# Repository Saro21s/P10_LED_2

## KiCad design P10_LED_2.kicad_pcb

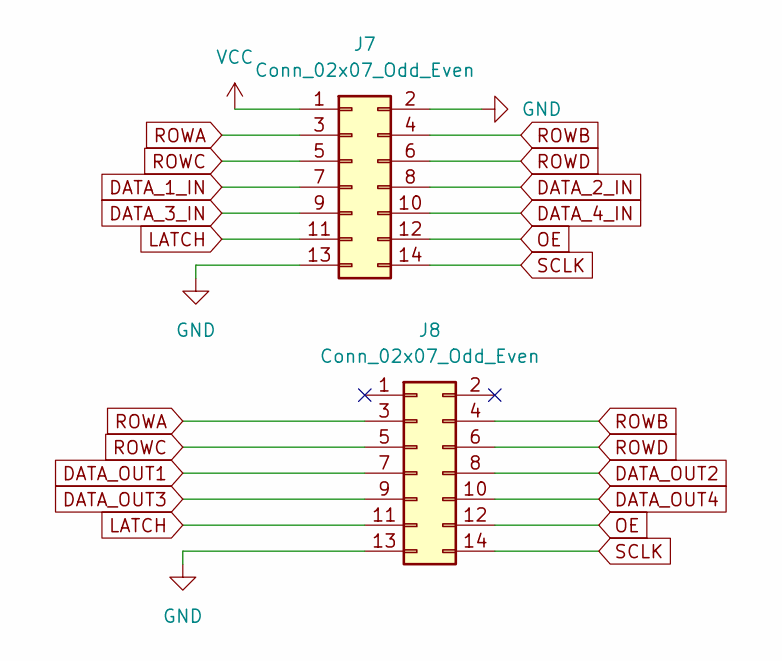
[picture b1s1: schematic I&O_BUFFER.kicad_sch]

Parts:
J7, J8: Conn_02x07_Odd_Even; PinHeader_2x07_P2.00mm_Vertical

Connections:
DATA_1_IN: J7.7; also elsewhere on the board
DATA_2_IN: J7.8; also elsewhere on the board
DATA_3_IN: J7.9; also elsewhere on the board
DATA_4_IN: J7.10; also elsewhere on the board
DATA_OUT1: J8.7; also elsewhere on the board
DATA_OUT2: J8.8; also elsewhere on the board
DATA_OUT3: J8.9; also elsewhere on the board
DATA_OUT4: J8.10; also elsewhere on the board
GND: J7.2, J7.13, J8.13; also elsewhere on the board
LATCH: J7.11, J8.11; also elsewhere on the board
OE: J7.12, J8.12; also elsewhere on the board
ROWA: J7.3, J8.3; also elsewhere on the board
ROWB: J7.4, J8.4; also elsewhere on the board
ROWC: J7.5, J8.5; also elsewhere on the board
ROWD: J7.6, J8.6; also elsewhere on the board
SCLK: J7.14, J8.14; also elsewhere on the board
VCC: J7.1; also elsewhere on the board

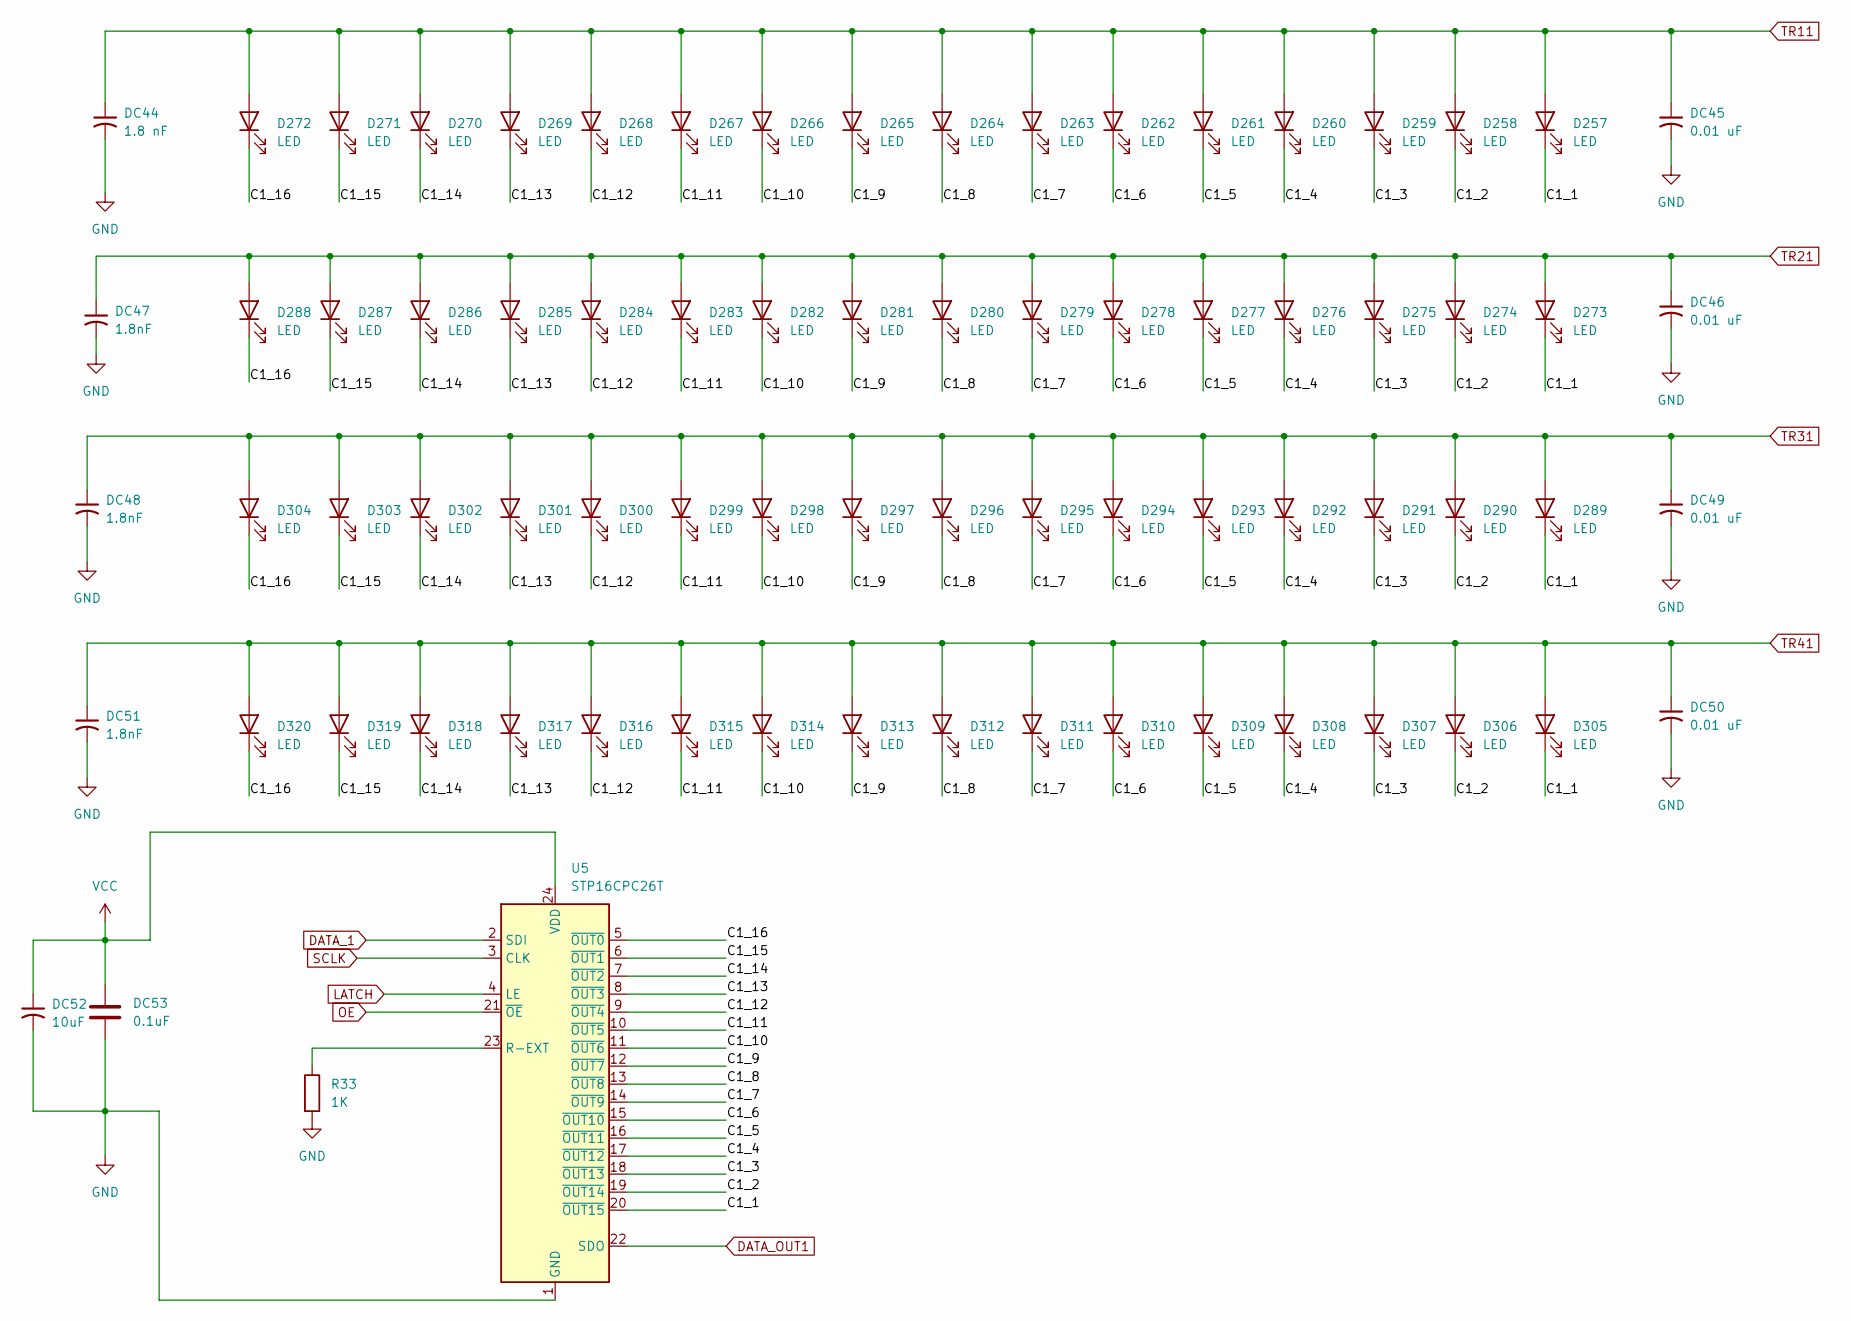
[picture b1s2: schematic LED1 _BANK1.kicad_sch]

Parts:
D257, D258, D259, D260, D261, D262, D263, D264, D265, D266, D267, D268, D269, D270, D271, D272, D273, D274, D275, D276, D277, D278, D279, D280, D281, D282, D283, D284, D285, D286, D287, D288, D289, D290, D291, D292, D293, D294, D295, D296, D297, D298, D299, D300, D301, D302, D303, D304, D305, D306, D307, D308, D309, D310, D311, D312, D313, D314, D315, D316, D317, D318, D319, D320: LED; LED_0805_2012Metric
DC44: 1.8 nF; C_0805_2012Metric
DC45, DC46, DC49, DC50: 0.01 uF; C_0805_2012Metric
DC47, DC48, DC51: 1.8nF; C_0805_2012Metric
DC52: 10uF; C_0805_2012Metric
DC53: 0.1uF; C_0805_2012Metric
R33: 1K; R_0805_2012Metric
U5: STP16CPC26T; TSSOP-24_4.4x7.8mm_P0.65mm

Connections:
/LED1 _BANK1/C1_1: D257.1 (K), D273.1 (K), D289.1 (K), D305.1 (K), U5.20 (~OUT15)
/LED1 _BANK1/C1_2: D258.1 (K), D274.1 (K), D290.1 (K), D306.1 (K), U5.19 (~OUT14)
/LED1 _BANK1/C1_3: D259.1 (K), D275.1 (K), D291.1 (K), D307.1 (K), U5.18 (~OUT13)
/LED1 _BANK1/C1_4: D260.1 (K), D276.1 (K), D292.1 (K), D308.1 (K), U5.17 (~OUT12)
/LED1 _BANK1/C1_5: D261.1 (K), D277.1 (K), D293.1 (K), D309.1 (K), U5.16 (~OUT11)
/LED1 _BANK1/C1_6: D262.1 (K), D278.1 (K), D294.1 (K), D310.1 (K), U5.15 (~OUT10)
/LED1 _BANK1/C1_7: D263.1 (K), D279.1 (K), D295.1 (K), D311.1 (K), U5.14 (~OUT9)
/LED1 _BANK1/C1_8: D264.1 (K), D280.1 (K), D296.1 (K), D312.1 (K), U5.13 (~OUT8)
/LED1 _BANK1/C1_9: D265.1 (K), D281.1 (K), D297.1 (K), D313.1 (K), U5.12 (~OUT7)
/LED1 _BANK1/C1_10: D266.1 (K), D282.1 (K), D298.1 (K), D314.1 (K), U5.11 (~OUT6)
/LED1 _BANK1/C1_11: D267.1 (K), D283.1 (K), D299.1 (K), D315.1 (K), U5.10 (~OUT5)
/LED1 _BANK1/C1_12: D268.1 (K), D284.1 (K), D300.1 (K), D316.1 (K), U5.9 (~OUT4)
/LED1 _BANK1/C1_13: D269.1 (K), D285.1 (K), D301.1 (K), D317.1 (K), U5.8 (~OUT3)
/LED1 _BANK1/C1_14: D270.1 (K), D286.1 (K), D302.1 (K), D318.1 (K), U5.7 (~OUT2)
/LED1 _BANK1/C1_15: D271.1 (K), D287.1 (K), D303.1 (K), D319.1 (K), U5.6 (~OUT1)
/LED1 _BANK1/C1_16: D272.1 (K), D288.1 (K), D304.1 (K), D320.1 (K), U5.5 (~OUT0)
DATA_1: U5.2 (SDI); also elsewhere on the board
DATA_OUT1: U5.22 (SDO); also elsewhere on the board
GND: DC44.2, DC45.2, DC46.2, DC47.2, DC48.2, DC49.2, DC50.2, DC51.2, DC52.2, DC53.2, R33.2, U5.1 (GND); also elsewhere on the board
LATCH: U5.4 (LE); also elsewhere on the board
unnamed: R33.1, U5.23 (R-EXT)
OE: U5.21 (~OE); also elsewhere on the board
SCLK: U5.3 (CLK); also elsewhere on the board
TR11: D257.2 (A), D258.2 (A), D259.2 (A), D260.2 (A), D261.2 (A), D262.2 (A), D263.2 (A), D264.2 (A), D265.2 (A), D266.2 (A), D267.2 (A), D268.2 (A), D269.2 (A), D270.2 (A), D271.2 (A), D272.2 (A), DC44.1, DC45.1; also elsewhere on the board
TR21: D273.2 (A), D274.2 (A), D275.2 (A), D276.2 (A), D277.2 (A), D278.2 (A), D279.2 (A), D280.2 (A), D281.2 (A), D282.2 (A), D283.2 (A), D284.2 (A), D285.2 (A), D286.2 (A), D287.2 (A), D288.2 (A), DC46.1, DC47.1; also elsewhere on the board
TR31: D289.2 (A), D290.2 (A), D291.2 (A), D292.2 (A), D293.2 (A), D294.2 (A), D295.2 (A), D296.2 (A), D297.2 (A), D298.2 (A), D299.2 (A), D300.2 (A), D301.2 (A), D302.2 (A), D303.2 (A), D304.2 (A), DC48.1, DC49.1; also elsewhere on the board
TR41: D305.2 (A), D306.2 (A), D307.2 (A), D308.2 (A), D309.2 (A), D310.2 (A), D311.2 (A), D312.2 (A), D313.2 (A), D314.2 (A), D315.2 (A), D316.2 (A), D317.2 (A), D318.2 (A), D319.2 (A), D320.2 (A), DC50.1, DC51.1; also elsewhere on the board
VCC: DC52.1, DC53.1, U5.24 (VDD); also elsewhere on the board

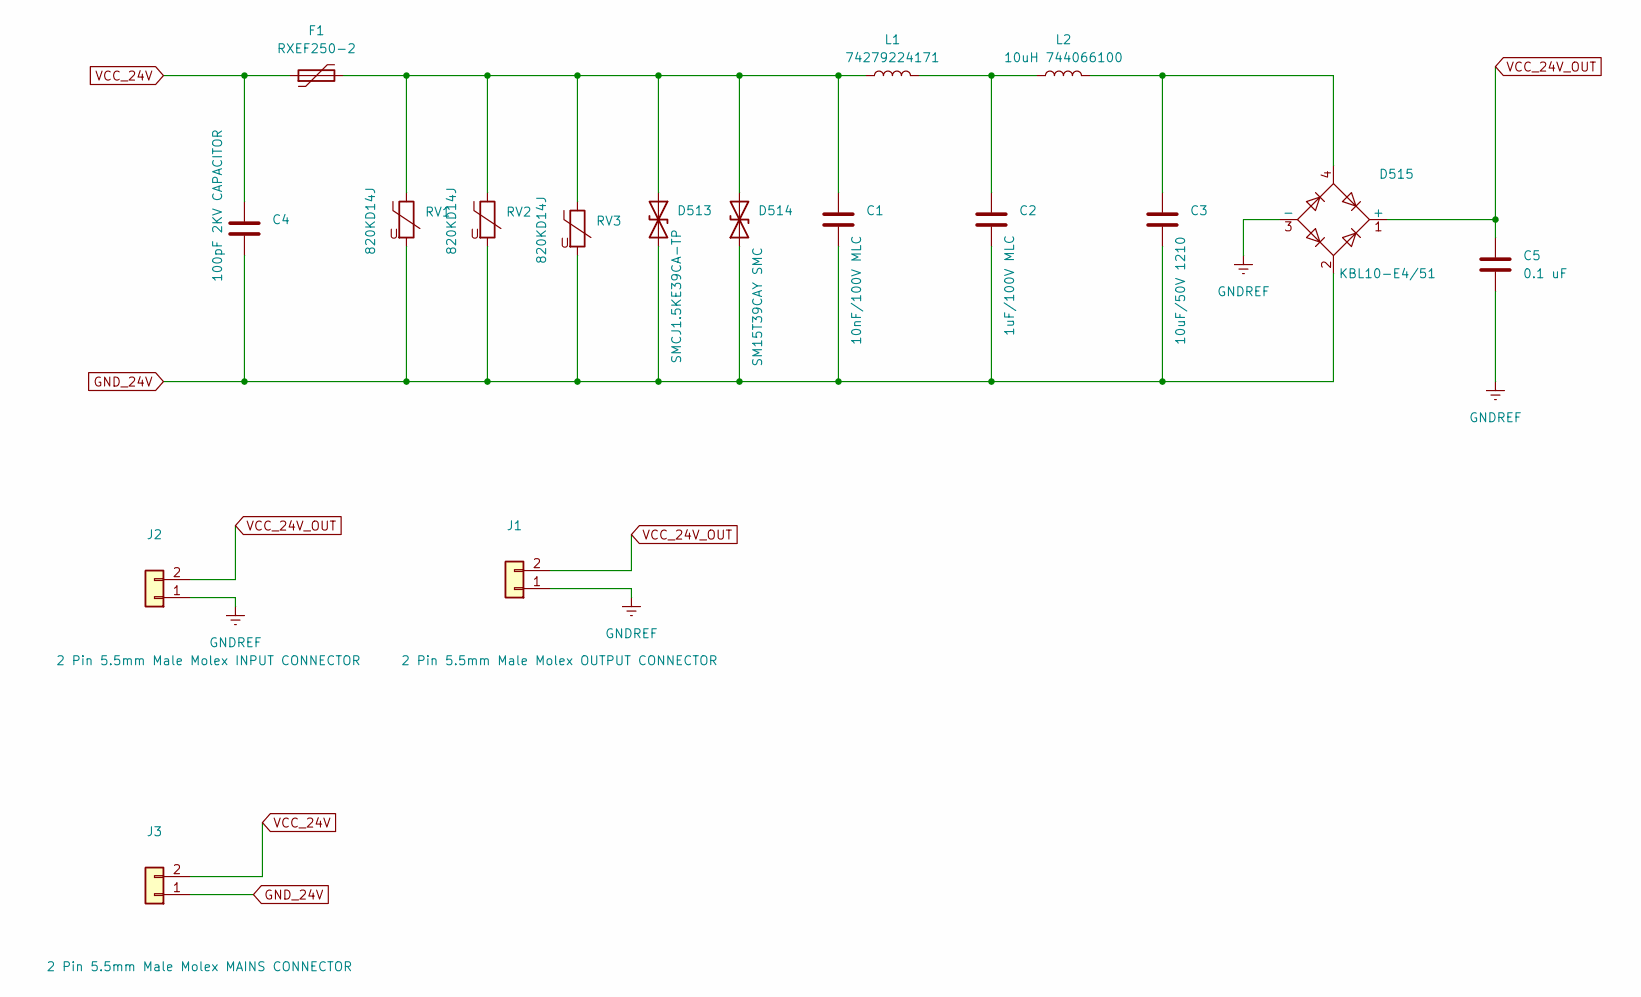
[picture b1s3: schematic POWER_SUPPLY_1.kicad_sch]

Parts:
C1: 10nF/100V MLC; C_1210_3225Metric
C2: 1uF/100V MLC; C_1210_3225Metric
C3: 10uF/50V 1210; C_0805_2012Metric
C4: 100pF 2KV CAPACITOR; C_0805_2012Metric
C5: 0.1 uF; C_1210_3225Metric
D513: SMCJ1.5KE39CA-TP; D_SMC
D514: SM15T39CAY SMC; D_SMC
D515: KBL10-E4/51; Diode_Bridge_Round_D9.8mm
F1: RXEF250-2; Fuse_1812_4532Metric
J1: 2 Pin 5.5mm Male Molex OUTPUT CONNECTOR; Molex_Mini-Fit_Jr_5569-02A1_2x01_P4.20mm_Horizontal
J2: 2 Pin 5.5mm Male Molex INPUT CONNECTOR; Molex_Mini-Fit_Jr_5569-02A1_2x01_P4.20mm_Horizontal
J3: 2 Pin 5.5mm Male Molex MAINS CONNECTOR; Molex_Mini-Fit_Jr_5569-02A1_2x01_P4.20mm_Horizontal
L1: 74279224171; L_1812_4532Metric
L2: 10uH 744066100; L_1812_4532Metric
RV1, RV2, RV3: 820KD14J; RV_Disc_D12mm_W5.8mm_P7.5mm

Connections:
GNDREF: C5.2, D515.3 (-), J1.1, J2.1; also elsewhere on the board
GND_24V: C1.2, C2.2, C3.2, C4.2, D513.2 (A2), D514.1 (A1), D515.2, J3.1, RV1.2, RV2.2, RV3.2
unnamed: C2.1, L1.2, L2.1
unnamed: C3.1, D515.4, L2.2
unnamed: C1.1, D513.1 (A1), D514.2 (A2), F1.2, L1.1, RV1.1, RV2.1, RV3.1
VCC_24V: C4.1, F1.1, J3.2
VCC_24V_OUT: C5.1, D515.1 (+), J1.2, J2.2; also elsewhere on the board

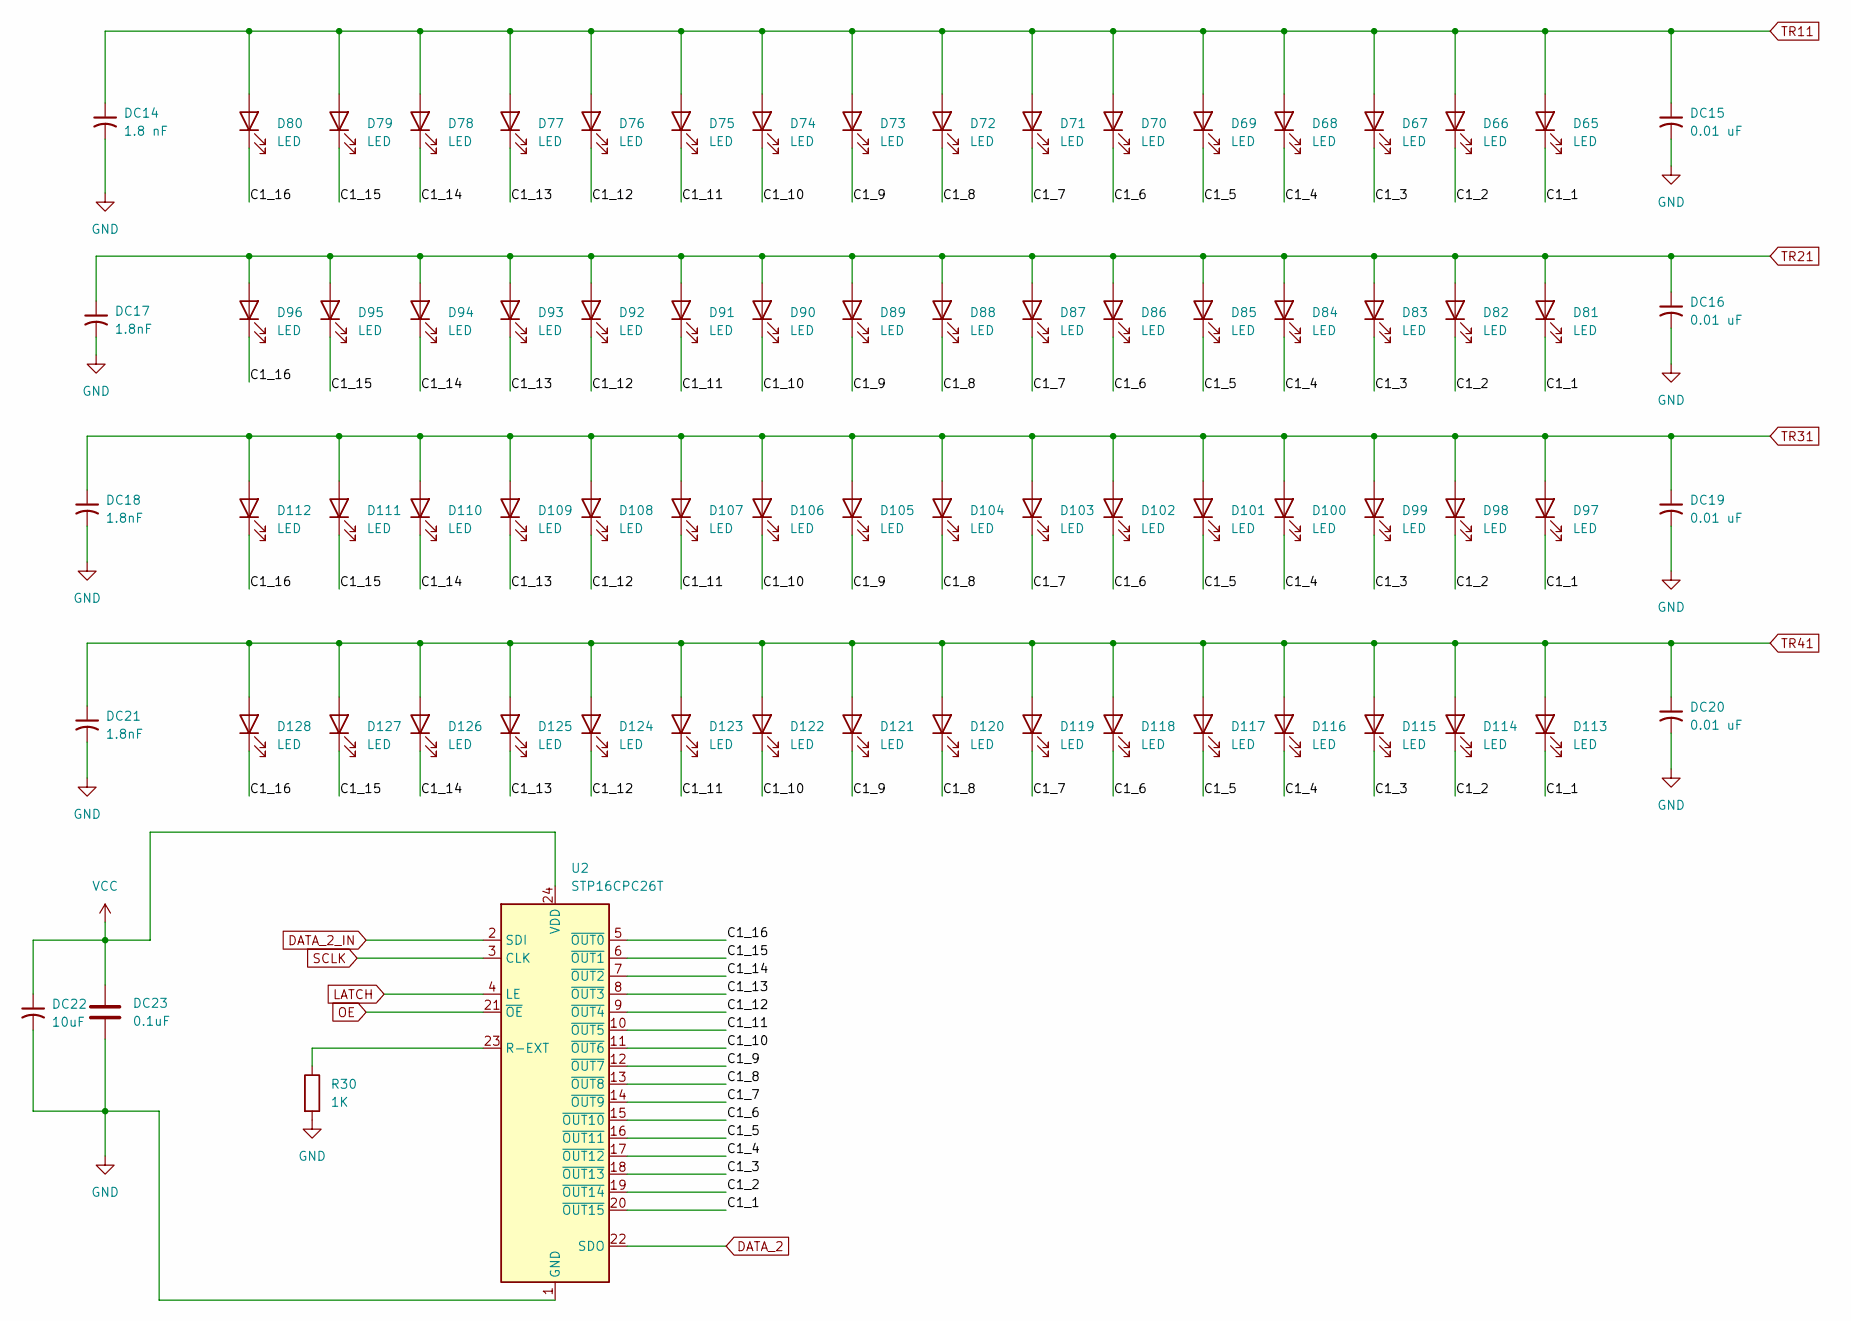
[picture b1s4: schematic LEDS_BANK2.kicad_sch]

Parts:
D65, D66, D67, D68, D69, D70, D71, D72, D73, D74, D75, D76, D77, D78, D79, D80, D81, D82, D83, D84, D85, D86, D87, D88, D89, D90, D91, D92, D93, D94, D95, D96, D97, D98, D99, D100, D101, D102, D103, D104, D105, D106, D107, D108, D109, D110, D111, D112, D113, D114, D115, D116, D117, D118, D119, D120, D121, D122, D123, D124, D125, D126, D127, D128: LED; LED_0805_2012Metric
DC14: 1.8 nF; C_0805_2012Metric
DC15, DC16, DC19, DC20: 0.01 uF; C_0805_2012Metric
DC17, DC18, DC21: 1.8nF; C_0805_2012Metric
DC22: 10uF; C_0805_2012Metric
DC23: 0.1uF; C_0805_2012Metric
R30: 1K; R_0805_2012Metric
U2: STP16CPC26T; TSSOP-24_4.4x7.8mm_P0.65mm

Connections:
/LEDS_BANK2/C1_1: D65.1 (K), D81.1 (K), D97.1 (K), D113.1 (K), U2.20 (~OUT15)
/LEDS_BANK2/C1_2: D66.1 (K), D82.1 (K), D98.1 (K), D114.1 (K), U2.19 (~OUT14)
/LEDS_BANK2/C1_3: D67.1 (K), D83.1 (K), D99.1 (K), D115.1 (K), U2.18 (~OUT13)
/LEDS_BANK2/C1_4: D68.1 (K), D84.1 (K), D100.1 (K), D116.1 (K), U2.17 (~OUT12)
/LEDS_BANK2/C1_5: D69.1 (K), D85.1 (K), D101.1 (K), D117.1 (K), U2.16 (~OUT11)
/LEDS_BANK2/C1_6: D70.1 (K), D86.1 (K), D102.1 (K), D118.1 (K), U2.15 (~OUT10)
/LEDS_BANK2/C1_7: D71.1 (K), D87.1 (K), D103.1 (K), D119.1 (K), U2.14 (~OUT9)
/LEDS_BANK2/C1_8: D72.1 (K), D88.1 (K), D104.1 (K), D120.1 (K), U2.13 (~OUT8)
/LEDS_BANK2/C1_9: D73.1 (K), D89.1 (K), D105.1 (K), D121.1 (K), U2.12 (~OUT7)
/LEDS_BANK2/C1_10: D74.1 (K), D90.1 (K), D106.1 (K), D122.1 (K), U2.11 (~OUT6)
/LEDS_BANK2/C1_11: D75.1 (K), D91.1 (K), D107.1 (K), D123.1 (K), U2.10 (~OUT5)
/LEDS_BANK2/C1_12: D76.1 (K), D92.1 (K), D108.1 (K), D124.1 (K), U2.9 (~OUT4)
/LEDS_BANK2/C1_13: D77.1 (K), D93.1 (K), D109.1 (K), D125.1 (K), U2.8 (~OUT3)
/LEDS_BANK2/C1_14: D78.1 (K), D94.1 (K), D110.1 (K), D126.1 (K), U2.7 (~OUT2)
/LEDS_BANK2/C1_15: D79.1 (K), D95.1 (K), D111.1 (K), D127.1 (K), U2.6 (~OUT1)
/LEDS_BANK2/C1_16: D80.1 (K), D96.1 (K), D112.1 (K), D128.1 (K), U2.5 (~OUT0)
DATA_2: U2.22 (SDO); also elsewhere on the board
DATA_2_IN: U2.2 (SDI); also elsewhere on the board
GND: DC14.2, DC15.2, DC16.2, DC17.2, DC18.2, DC19.2, DC20.2, DC21.2, DC22.2, DC23.2, R30.2, U2.1 (GND); also elsewhere on the board
LATCH: U2.4 (LE); also elsewhere on the board
unnamed: R30.1, U2.23 (R-EXT)
OE: U2.21 (~OE); also elsewhere on the board
SCLK: U2.3 (CLK); also elsewhere on the board
TR11: D65.2 (A), D66.2 (A), D67.2 (A), D68.2 (A), D69.2 (A), D70.2 (A), D71.2 (A), D72.2 (A), D73.2 (A), D74.2 (A), D75.2 (A), D76.2 (A), D77.2 (A), D78.2 (A), D79.2 (A), D80.2 (A), DC14.1, DC15.1; also elsewhere on the board
TR21: D81.2 (A), D82.2 (A), D83.2 (A), D84.2 (A), D85.2 (A), D86.2 (A), D87.2 (A), D88.2 (A), D89.2 (A), D90.2 (A), D91.2 (A), D92.2 (A), D93.2 (A), D94.2 (A), D95.2 (A), D96.2 (A), DC16.1, DC17.1; also elsewhere on the board
TR31: D97.2 (A), D98.2 (A), D99.2 (A), D100.2 (A), D101.2 (A), D102.2 (A), D103.2 (A), D104.2 (A), D105.2 (A), D106.2 (A), D107.2 (A), D108.2 (A), D109.2 (A), D110.2 (A), D111.2 (A), D112.2 (A), DC18.1, DC19.1; also elsewhere on the board
TR41: D113.2 (A), D114.2 (A), D115.2 (A), D116.2 (A), D117.2 (A), D118.2 (A), D119.2 (A), D120.2 (A), D121.2 (A), D122.2 (A), D123.2 (A), D124.2 (A), D125.2 (A), D126.2 (A), D127.2 (A), D128.2 (A), DC20.1, DC21.1; also elsewhere on the board
VCC: DC22.1, DC23.1, U2.24 (VDD); also elsewhere on the board

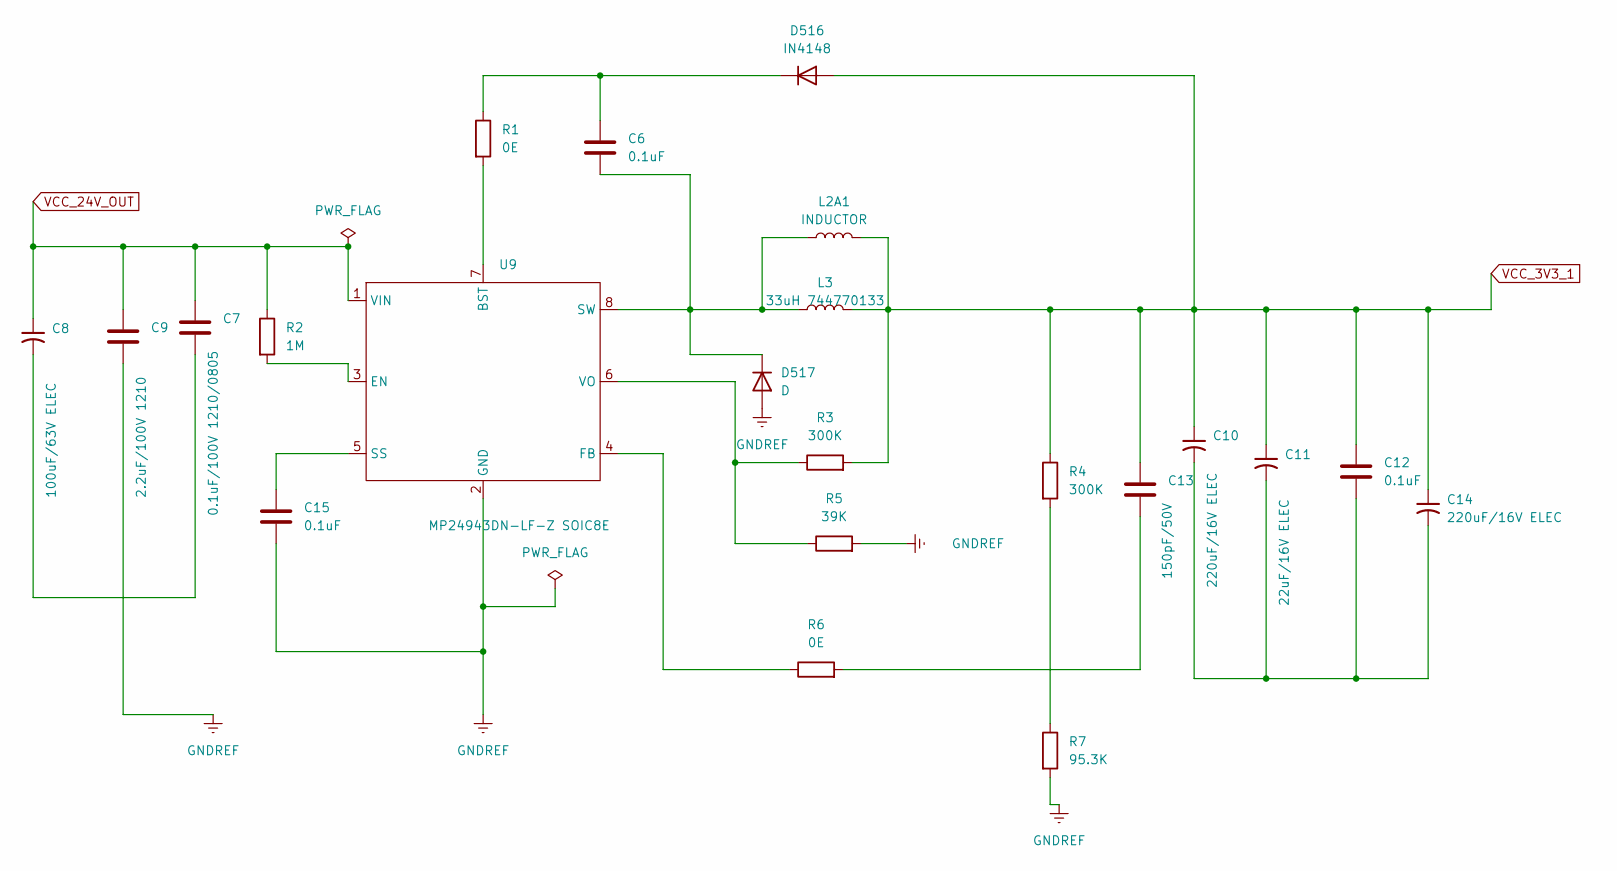
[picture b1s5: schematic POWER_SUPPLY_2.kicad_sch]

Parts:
C6, C12, C15: 0.1uF; C_0805_2012Metric
C7: 0.1uF/100V 1210/0805; C_0805_2012Metric
C8: 100uF/63V ELEC; C_0805_2012Metric
C9: 2.2uF/100V 1210; C_0805_2012Metric
C10, C14: 220uF/16V ELEC; C_0805_2012Metric
C11: 22uF/16V ELEC; C_0805_2012Metric
C13: 150pF/50V; C_0805_2012Metric
D516: IN4148; D_SOD-123
D517: D; D_SOD-123
L2A1: INDUCTOR; L_1812_4532Metric
L3: 33uH 744770133; L_1812_4532Metric
R1, R6: 0E; R_0805_2012Metric
R2: 1M; R_0805_2012Metric
R3, R4: 300K; R_0805_2012Metric
R5: 39K; R_0805_2012Metric
R7: 95.3K; R_0805_2012Metric
U9: MP24943DN-LF-Z SOIC8E; SOIC-8_3.9x4.9mm_P1.27mm

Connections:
GNDREF: C9.2, C15.2, D517.2 (A), R5.2, R7.2, U9.2 (GND); also elsewhere on the board
unnamed: C7.2, C8.2
unnamed: C10.2, C11.2, C12.2, C14.2
unnamed: C13.2, R6.2
unnamed: C6.1, D516.1 (K), R1.1
unnamed: C6.2, D517.1 (K), L2A1.1, L3.1, U9.8 (SW)
unnamed: R4.2, R7.1
unnamed: R1.2, U9.7 (BST)
unnamed: R2.2, U9.3 (EN)
unnamed: R6.1, U9.4 (FB)
unnamed: C15.1, U9.5 (SS)
unnamed: R3.1, R5.1, U9.6 (VO)
VCC_3V3_1: C10.1, C11.1, C12.1, C13.1, C14.1, D516.2 (A), L2A1.2, L3.2, R3.2, R4.1; also elsewhere on the board
VCC_24V_OUT: C7.1, C8.1, C9.1, R2.1, U9.1 (VIN); also elsewhere on the board

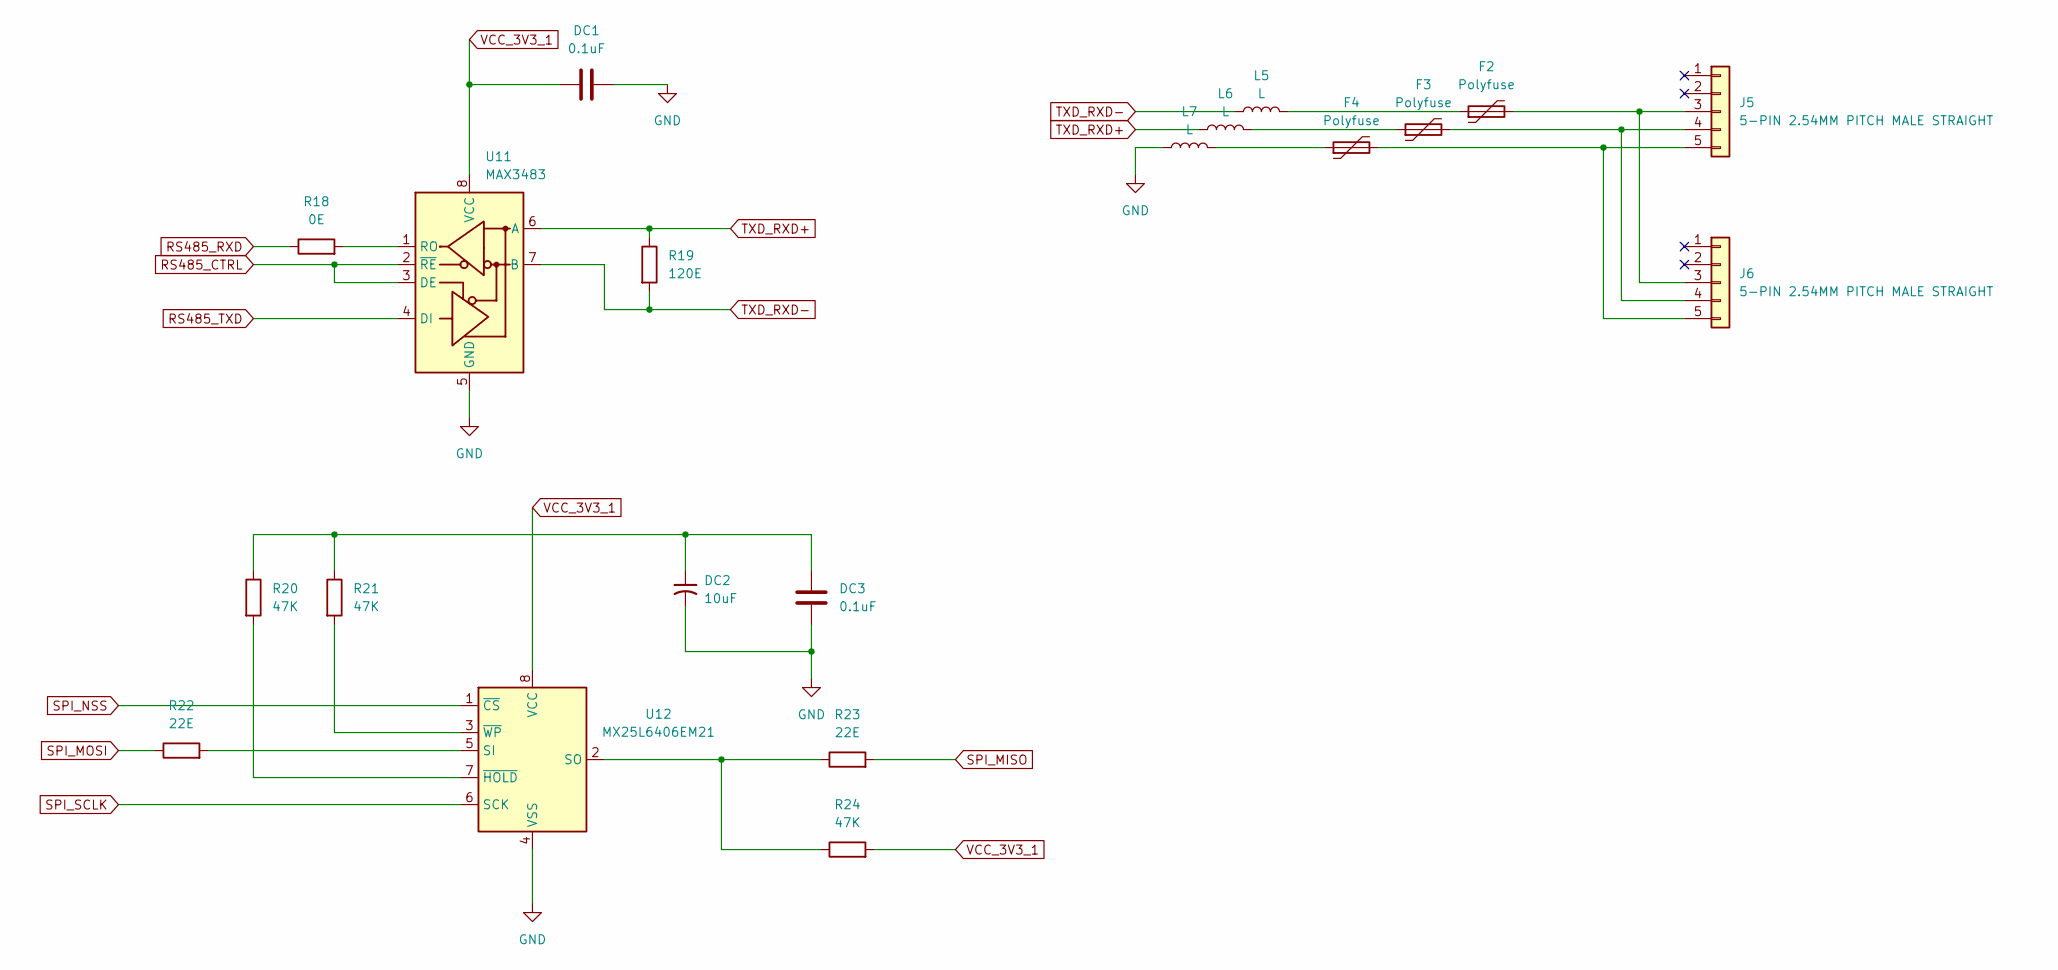
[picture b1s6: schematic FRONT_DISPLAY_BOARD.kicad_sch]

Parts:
DC1, DC3: 0.1uF; C_0805_2012Metric
DC2: 10uF; C_0805_2012Metric
F2, F3, F4: Polyfuse; Fuse_1206_3216Metric
J5, J6: 5-PIN 2.54MM PITCH MALE STRAIGHT; PinHeader_1x05_P2.54mm_Vertical
L5, L6, L7: L; L_0805_2012Metric
R18: 0E; R_0805_2012Metric
R19: 120E; R_1206_3216Metric
R20, R21, R24: 47K; R_0805_2012Metric
R22, R23: 22E; R_0805_2012Metric
U11: MAX3483; SOIC-8_3.9x4.9mm_P1.27mm
U12: MX25L6406EM21; SOIC-8-1EP_3.9x4.9mm_P1.27mm_EP2.29x3mm

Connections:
GND: DC1.2, DC2.2, DC3.2, L7.1, U11.5 (GND), U12.4 (VSS); also elsewhere on the board
unnamed: DC2.1, DC3.1, R20.1, R21.1
unnamed: F2.1, L5.2
unnamed: F3.1, L6.2
unnamed: F4.1, L7.2
unnamed: F2.2, J5.3, J6.3
unnamed: F3.2, J5.4, J6.4
unnamed: F4.2, J5.5, J6.5
unnamed: R18.2, U11.1 (RO)
unnamed: R22.2, U12.5 (SI)
unnamed: R23.1, R24.1, U12.2 (SO)
unnamed: R20.2, U12.7 (~HOLD)
unnamed: R21.2, U12.3 (~WP)
RS485_CTRL: U11.2 (~RE), U11.3 (DE); also elsewhere on the board
RS485_RXD: R18.1; also elsewhere on the board
RS485_TXD: U11.4 (DI); also elsewhere on the board
SPI_MISO: R23.2; also elsewhere on the board
SPI_MOSI: R22.1; also elsewhere on the board
SPI_NSS: U12.1 (~CS); also elsewhere on the board
SPI_SCLK: U12.6 (SCK); also elsewhere on the board
TXD_RXD+: L6.1, R19.1, U11.6 (A)
TXD_RXD-: L5.1, R19.2, U11.7 (B)
VCC_3V3_1: DC1.1, R24.2, U11.8 (VCC), U12.8 (VCC); also elsewhere on the board

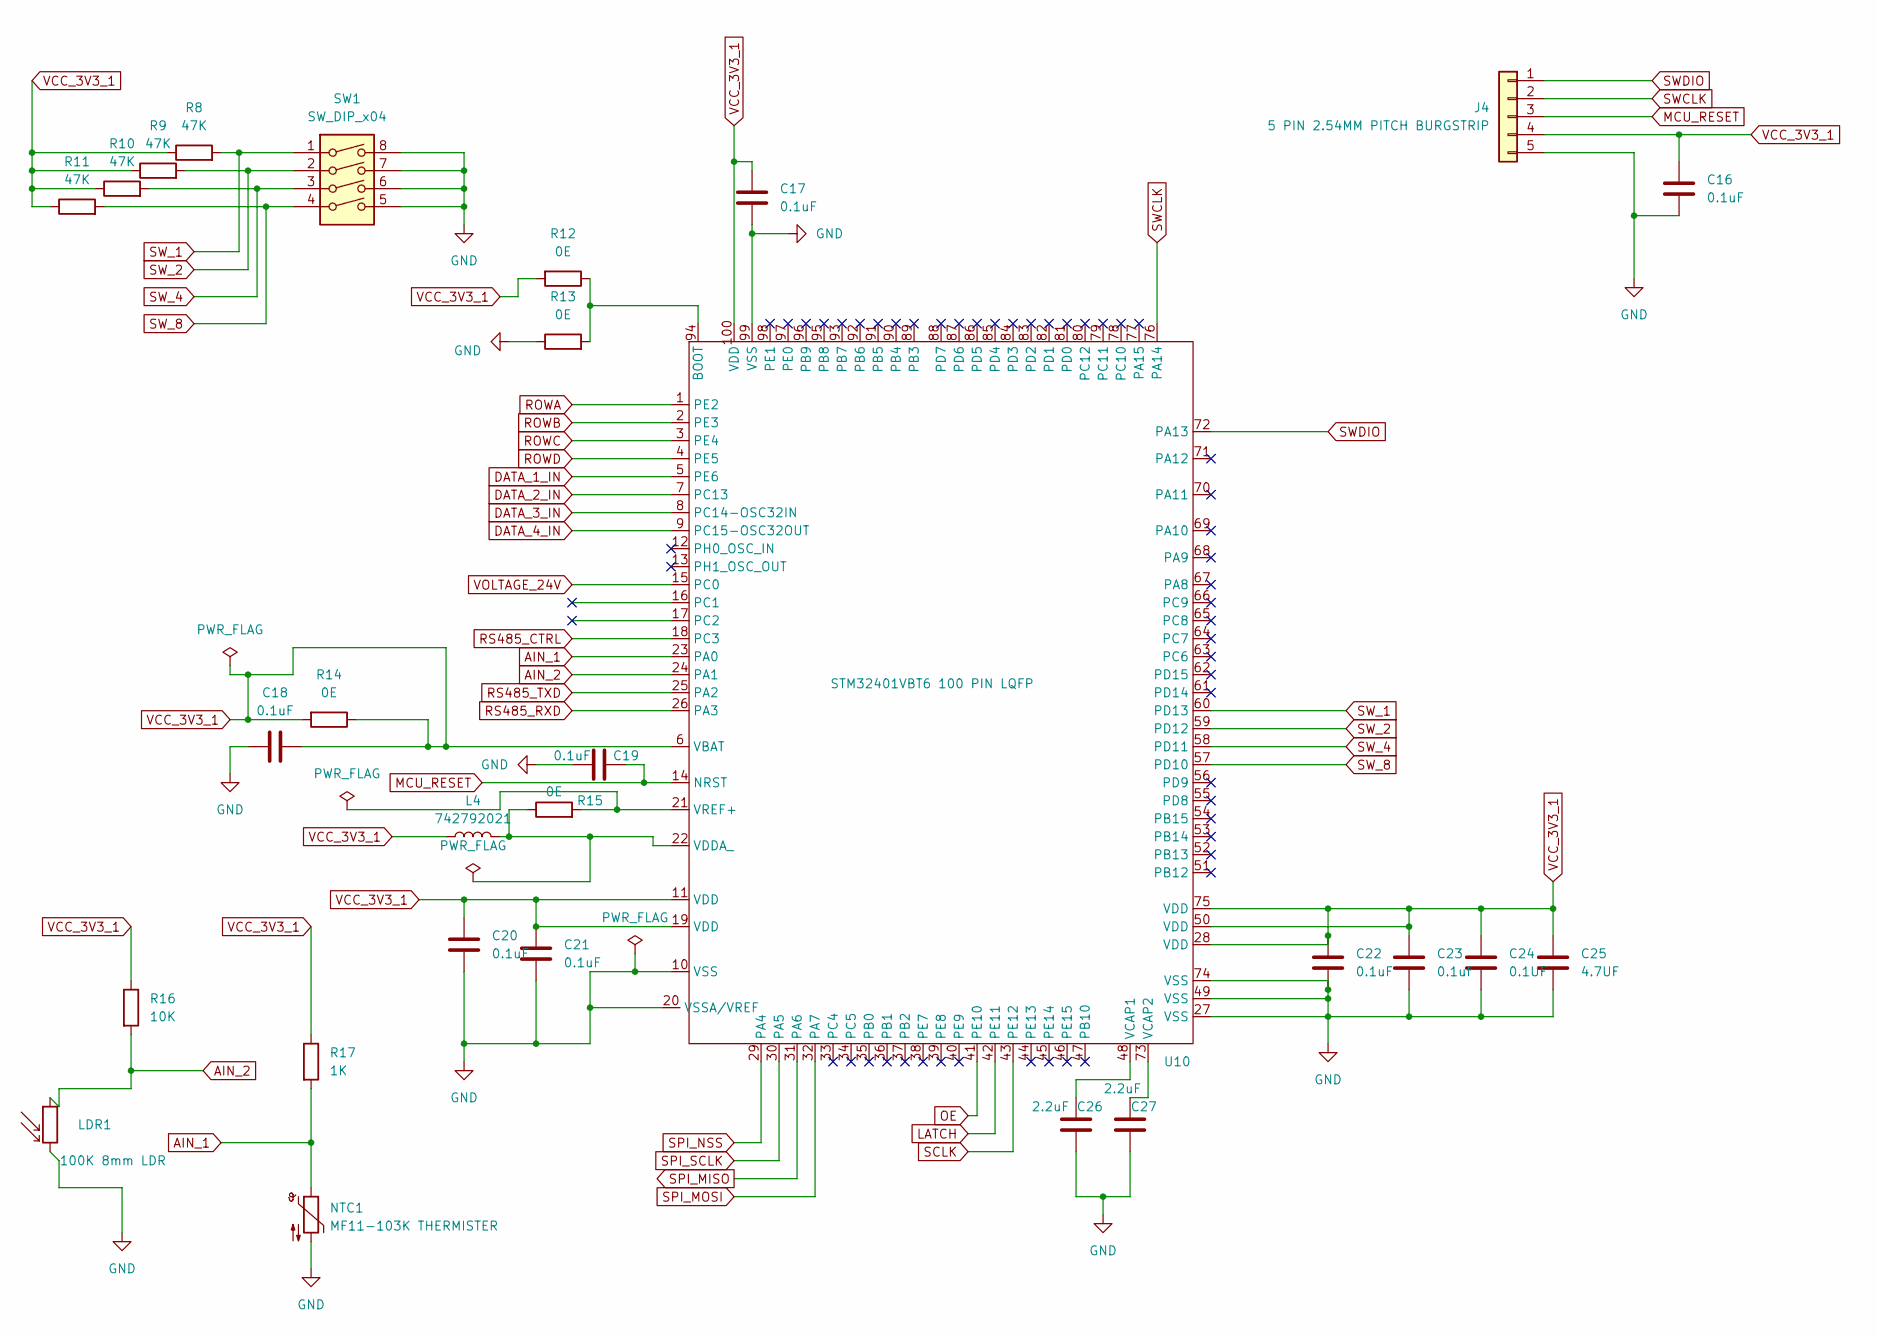
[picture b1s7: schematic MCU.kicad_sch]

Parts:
C16, C17, C18, C19, C20, C21, C22: 0.1uF; C_0805_2012Metric
C23: 0.1uf; C_0805_2012Metric
C24: 0.1UF; C_0805_2012Metric
C25: 4.7UF; C_0805_2012Metric
C26, C27: 2.2uF; C_0805_2012Metric
J4: 5 PIN 2.54MM PITCH BURGSTRIP; PinHeader_1x05_P2.54mm_Vertical
L4: 742792021; L_0805_2012Metric
LDR1: 100K 8mm LDR; R_LDR_10x8.5mm_P7.6mm_Vertical
NTC1: MF11-103K THERMISTER; R_Axial_DIN0207_L6.3mm_D2.5mm_P7.62mm_Horizontal
R8, R9, R10, R11: 47K; R_0805_2012Metric
R12, R13, R14, R15: 0E; R_0805_2012Metric
R16: 10K; R_0805_2012Metric
R17: 1K; R_0805_2012Metric
SW1: SW_DIP_x04; SW_DIP_SPSTx04_Slide_9.78x12.34mm_W8.61mm_P2.54mm
U10: STM32401VBT6 100 PIN LQFP; LQFP-100_14x14mm_P0.5mm

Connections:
AIN_1: NTC1.1, R17.2, U10.23 (PA0)
AIN_2: LDR1.1, R16.2, U10.24 (PA1)
DATA_1_IN: U10.5 (PE6); also elsewhere on the board
DATA_2_IN: U10.7 (PC13); also elsewhere on the board
DATA_3_IN: U10.8 (PC14-OSC32IN); also elsewhere on the board
DATA_4_IN: U10.9 (PC15-OSC32OUT); also elsewhere on the board
GND: C16.2, C17.1, C18.2, C19.2, C20.2, C21.2, C22.2, C23.2, C24.2, C25.2, C26.2, C27.2, J4.5, LDR1.2, NTC1.2, R13.1, SW1.5, SW1.6, SW1.7, SW1.8, U10.10 (VSS), U10.20 (VSSA/VREF), U10.27 (VSS), U10.49 (VSS), U10.74 (VSS), U10.99 (VSS); also elsewhere on the board
LATCH: U10.42 (PE11); also elsewhere on the board
MCU_RESET: C19.1, J4.3, U10.14 (NRST)
unnamed: R12.1, R13.2, U10.94 (BOOT)
unnamed: C26.1, U10.48 (VCAP1)
unnamed: C27.1, U10.73 (VCAP2)
unnamed: L4.2, R15.1, U10.22 (VDDA_)
unnamed: R15.2, U10.21 (VREF+)
OE: U10.41 (PE10); also elsewhere on the board
ROWA: U10.1 (PE2); also elsewhere on the board
ROWB: U10.2 (PE3); also elsewhere on the board
ROWC: U10.3 (PE4); also elsewhere on the board
ROWD: U10.4 (PE5); also elsewhere on the board
RS485_CTRL: U10.18 (PC3); also elsewhere on the board
RS485_RXD: U10.26 (PA3); also elsewhere on the board
RS485_TXD: U10.25 (PA2); also elsewhere on the board
SCLK: U10.43 (PE12); also elsewhere on the board
SPI_MISO: U10.31 (PA6); also elsewhere on the board
SPI_MOSI: U10.32 (PA7); also elsewhere on the board
SPI_NSS: U10.29 (PA4); also elsewhere on the board
SPI_SCLK: U10.30 (PA5); also elsewhere on the board
SWCLK: J4.2, U10.76 (PA14)
SWDIO: J4.1, U10.72 (PA13)
SW_1: R8.2, SW1.1, U10.60 (PD13)
SW_2: R9.2, SW1.2, U10.59 (PD12)
SW_4: R10.2, SW1.3, U10.58 (PD11)
SW_8: R11.2, SW1.4, U10.57 (PD10)
VCC_3V3_1: C16.1, C17.2, C18.1, C20.1, C21.1, C22.1, C23.1, C24.1, C25.1, J4.4, L4.1, R8.1, R9.1, R10.1, R11.1, R12.2, R14.1, R14.2, R16.1, R17.1, U10.6 (VBAT), U10.11 (VDD), U10.19 (VDD), U10.28 (VDD), U10.50 (VDD), U10.75 (VDD), U10.100 (VDD); also elsewhere on the board
VOLTAGE_24V: U10.15 (PC0)
